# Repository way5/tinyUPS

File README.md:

<h1>

`tinyUPS` a tiny toolkit for your UPS

</h1>

<p align="center" style="text-align:center">

&nbsp;&nbsp;&nbsp;&nbsp;&nbsp;&nbsp;

</p>

## **+ DESCRIPTION**

**tinyUPS** is the way to extend functionality of an Uninterruptible Power Supply (UPS)/power inverters.
It provides onboard SNMP server, temperature control and a Control Panel (CP), just like on an enterprise systems.
The project is now on beta test stage, however it shows very stable results during months 24/7. If you'll decide to modify your own UPS it's at your own risk.

<table cellpadding="0" cellspacing="0" width="100%">
<tr style="border-bottom: 1px solid;">
<td width="50px" style="text-align:center; padding-top:20px;">

</td>
<td>

This project requires advanced skills in electronics. It's not a plug-n-play device. ;)

</td>
</tr>
<tr>
<td style="text-align:center; padding-top:20px;">

</td>
<td>

**Follow the standard precautions! Uninterruptible Power Supply (UPS) is a potentially dangerous device as it contains electric parts under high voltage.**

</td>
</tr>
</table>

## **+ TABLE OF CONTENTS**

+ [**+ DESCRIPTION**](#-description)
+ [**+ TABLE OF CONTENTS**](#-table-of-contents)
+ [**+ TOOLKIT**](#-toolkit)
  + [- CONTROLLER](#--controller)
  + [- PCB](#--pcb)
  + [- Web UI](#--web-ui)
+ [**+ BUILD**](#-build)
  + [- CONFIGURATION](#--configuration)
  + [- WiFi CONNECTION STRATEGIES](#--wifi-connection-strategies)
+ [**+ SETUP**](#-setup)
+ [**+ CONTROL PANEL**](#-control-panel)
+ [**+ DEVELOPMENT**](#-development)
  + [- DRIVERS](#--drivers)
  + [- DEBUG](#--debug)
+ [**+ PHOTOS**](#-photos)
+ [**+ CREDITS**](#-credits)

## **+ TOOLKIT**

- PlatformIO
- KiCAD

### - CONTROLLER
**tinyUPS** is originally based on [WEMOS S2 mini](https://www.wemos.cc/en/latest/s2/s2_mini.html) board. However, very likely it would work on another ESP32 boards with minor changes in firmware.
All the configuration you may need is in [platformio.ini](platformio.ini) and the UPS driver header file. If the communication interface of a particular UPS is not SPI, you need to create a new UPS driver and to change the PCB as well.

<table cellpadding="0" cellspacing="0" width="100%">
<tr>
<td width="50px" style="text-align:center; padding-top:20px;">

</td>
<td>

If you've created a new driver please share it by creating merge request or attaching it in discussions.

</td>
</tr>
</table>

### - PCB
The [current PCB](schematics/CAM/tinyUPS.kicad_pcb) is designed for DIY via CAM method. If you want it printed profesionally, you may need to redesign the PCB.
Since the most of the UPS controllers have 5V data bus, we need a level shifter to be able to communicate with them and a small step-down PSU for ESP32.

[Bill of materials](schematics/CAM/tinyUPS.csv). Instead of the BSS138 mosfets could be used any compatible type, ex.: IRLML2502.

If you'll be using `S2 mini` board you need to desolder built-in LDO IC (ME6211C33) since power will be supplied directly to 3.3V pin. It's possible to keep the LDO but you will not be able to use serial port for firmware upload and debugging. See [WEMOS S2 mini schematics](schematics/sch_s2_mini_v1.0.0.pdf).

The example driver is for a built in SPI LCD display, for a particular manufacturer and model.
You'll probably have the very different device and may be even without any LCD display, so you'd need to figure out how to speak with the controller. This part is DIY. Feel free to call for help in [Discussions](https://github.com/way5/tinyUPS/discussions).

### - Web UI

UI translations are available in [./web/lang](./web/lang) directory. You can add new translation or remove existing if you wish by editing the header of [i18n.js](web/src/includes/i18n.js) script. Variable `i18nlang` contains the list of available locales to be built-in, where element 0 of the array is also a fallback (used by default) locale. Remove unnecessary locales from `i18nlang` to save space on file system partition.

The package manager is `yarn` so if you're not familiar with it continue with the folowing to build the UI:

```bash
yarn build:prod
```

that's all you need to prepare the FS partition to upload. Use `Upload Filesystem Image` command from `PlatformIO` project tasks or:

```bash
platformio run --target uploadfs [--environment [your_env]]
```

## **+ BUILD**

### - CONFIGURATION

All sigificant parameters for your setup are inside [configrure.json](./configure.json) file. If you're adding a new parameter you'd need to run `Rebuild Intellisense Index` in PlatformIO in order to have your parameter set and available.

| PARAMETER | DESCRIPTION |
|:---|:---|
| system_log_size | Size of the system log file (in bytes) |
| snmp_log_size | Size of the SNMP server log file (in bytes) |
| mtemp_log_size | Size of the temperature management log (in bytes) |
| mdata_log_size | Size of the log of monitored events (in bytes) |
| ups_rated_input_voltage | Nominal input voltage value (V) |
| ups_rated_input_freq | Nominal input frequency (Hz) |
| ups_rated_low_input_voltage_threshold | Nominal low threshold of the input voltage (V) |
| ups_rated_high_input_voltage_threshold | Nominal hight threshold for input voltage (V) |
| ups_rated_output_voltage | Nominal output voltage (V) |
| ups_rated_output_freq | Nominal output frequency (Hz) |
| battery_rated_charge_capacity_ah | Nominal UPS battery capacity (Ah) |
| ups_rated_battery_amps_max | Nominal UPS battery current (Amps) |
| wifi_reconnect_method | WiFi reconnection method (`see below`) |
| wifi_discovered_length | Max. length of the data array of discovered APs |

### - WiFi CONNECTION STRATEGIES

If **tinyUPS** has lost connection with AP you may wish it to fallback to AP mode (`tinyUPS.01.XXXX` network name) or it may keep trying to reconnect till the source network is available.
You can choose the desired behavior (see `wifi_reconnect_method` parameter) before to compile firmware.

| METHOD_ID | DESCRIPTION |
|:---:|:---|
| 1 | If the configuration data is available, **tinyUPS** intents to connect to the specified AP. If the connection is not succeeded it starts AP. If connection is lost the device tryes to reconnect once (10 sec interval). If connection is not succeeded it starts AP and remains in this mode until restart. |
|  2 <sub>[D]</sub> | If **tinyUPS** has lost connection with source network it tryes to reconnect once. If connection is not succeeded it starts AP and periodically scans WiFi networks. If the source network has found, the device intents to reconnect. Unless the connection is succeeded it remains in AP mode. |
| 3 | Once the device has lost connection to AP it continuously tryes to reconnect to the source network. The WiFi mode remains STA. |
| 4 | Rely on built-in functionality of `setAutoReconnect()`. **tinyUPS** will remain in STA mode and be seeking for the source AP. |

>***[D]*** - the default method

## **+ SETUP**
When you first run **tinyUPS**, it boots up in AP mode. Look for `tinyUPS.01.XXXX` WiFi network. Default network password (config.apkey) could be changed in [helpers.h](src/helpers.h). Once connected the configuration is available on 192.168.4.1.

When setup is completed **tinyUPS** restarts, expecting an automatically assigned IP.

You are able to restart the device or reset configuration data to defaults using Control Panel -> Service Menu:

and then continue with confirmation:

## **+ CONTROL PANEL**

The UI is pretty simple and displays most of the real-time parameters. There are multiple self explanatory graphical representations for the collected data.

 After successful setup it is highly recommended to change the `AP key` and generate the `device serial number`. Both options and corresponding controls you can find in `Settings` -> `Security` tab and `SNMP` tab respectively.

## **+ DEVELOPMENT**

### - DRIVERS
There are the following functions that must be implemented by every UPS driver: `upsDriverInit, upsDriverLoop, upsDriverDeinit`.
You may also wish to look at the driver for thermistor (currently this is 1k M52A), it may need some changes. Depends on which thermistor you'll be using.

### - DEBUG
Serial monitor is used to perform the most of the tasks and to solve issues. Once you've connected use `?` to list available commands.

## **+ PHOTOS**

|  |  |  |  |  |
|:---:|:---:|:---:|:---:|:---:|

## **+ CREDITS**

- Arduino [SNMP agent](https://github.com/0neblock/Arduino_SNMP) by #0neblock
- [ESPAsyncWebServer](https://github.com/me-no-dev/ESPAsyncWebServer)
- Icons by [Tabler Icons](https://tabler.io/)

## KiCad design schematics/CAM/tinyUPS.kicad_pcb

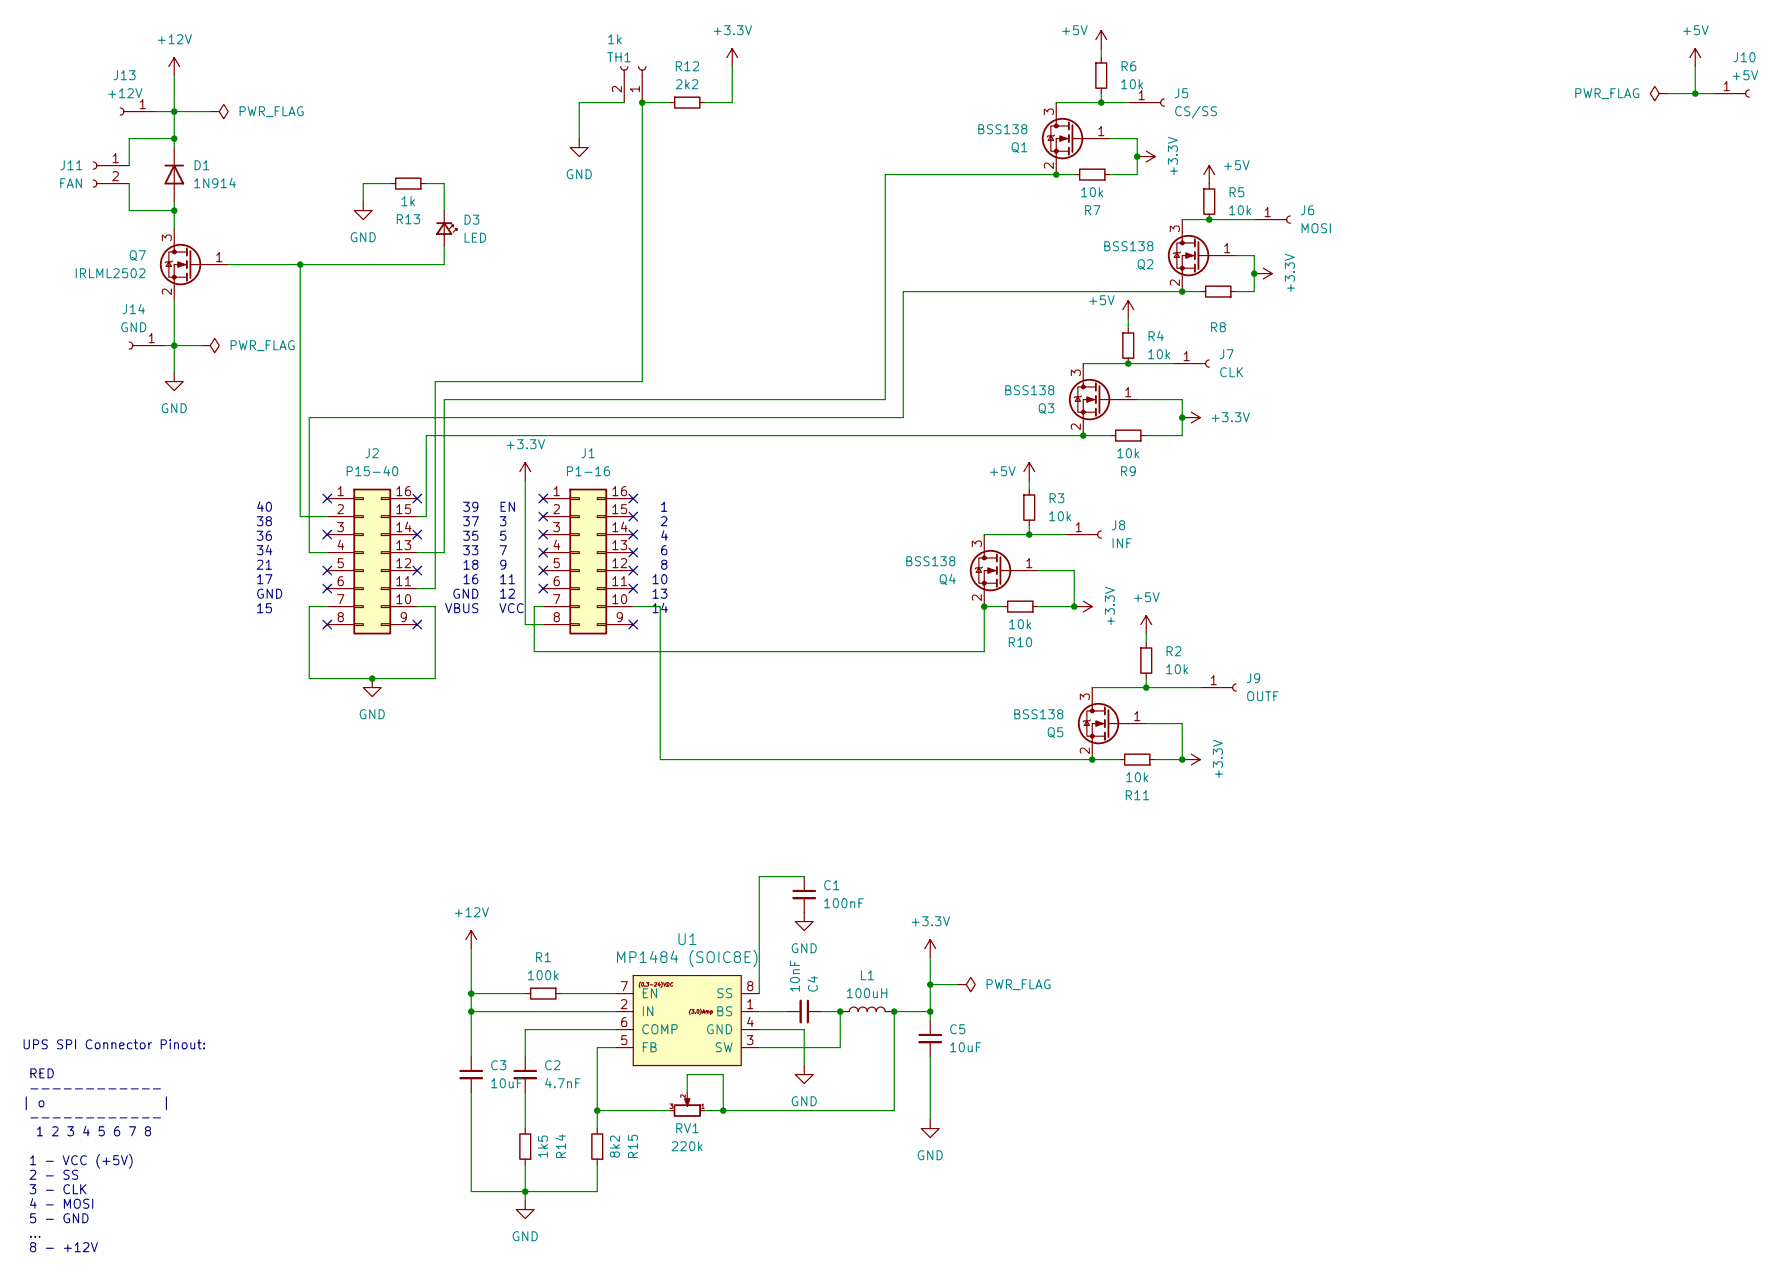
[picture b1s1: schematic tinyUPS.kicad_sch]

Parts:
C1: 100nF; C_1206_3216Metric_Pad1.33x1.80mm_HandSolder
C2: 4.7nF; C_1206_3216Metric_Pad1.33x1.80mm_HandSolder
C3, C5: 10uF; C_1206_3216Metric_Pad1.33x1.80mm_HandSolder
C4: 10nF; C_1206_3216Metric_Pad1.33x1.80mm_HandSolder
D1: 1N914; D_1210_3225Metric_Pad1.42x2.65mm_HandSolder
D3: LED; LED_1206_3216Metric_Pad1.42x1.75mm_HandSolder
J1: P1-16; PinHeader_2x08_P2.54mm_Vertical
J2: P15-40; PinHeader_2x08_P2.54mm_Vertical
J5: CS/SS; PinHeader_1x01_P2.54mm_Vertical
J6: MOSI; PinHeader_1x01_P2.54mm_Vertical
J7: CLK; PinHeader_1x01_P2.54mm_Vertical
J8: INF; PinHeader_1x01_P2.54mm_Vertical
J9: OUTF; PinHeader_1x01_P2.54mm_Vertical
J10: +5V; PinHeader_1x01_P2.54mm_Vertical
J11: FAN; PinHeader_1x02_P2.54mm_Vertical
J13: +12V; PinHeader_1x01_P2.54mm_Vertical
J14: GND; PinHeader_1x01_P2.54mm_Vertical
L1: 100uH; L_Bourns-SRN8040_8x8.15mm
Q1, Q2, Q3, Q4, Q5: BSS138; SOT-23_Handsoldering
Q7: IRLML2502; SOT-23W_Handsoldering
R1: 100k; R_1206_3216Metric_Pad1.30x1.75mm_HandSolder
R2, R3, R4, R5, R6, R7, R8, R9, R10, R11: 10k; R_1206_3216Metric_Pad1.30x1.75mm_HandSolder
R12: 2k2; R_Axial_DIN0207_L6.3mm_D2.5mm_P7.62mm_Horizontal
R13: 1k; R_1206_3216Metric_Pad1.30x1.75mm_HandSolder
R14: 1k5; R_1206_3216Metric_Pad1.30x1.75mm_HandSolder
R15: 8k2; R_1206_3216Metric_Pad1.30x1.75mm_HandSolder
RV1: 220k; Potentiometer_Bourns_3224W_Vertical
TH1: 1k; PinHeader_1x02_P2.54mm_Vertical
U1: MP1484 (SOIC8E); SOIC-8_3.9x4.9mm_P1.27mm

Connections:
+3.3V: C5.1, J1.8, L1.2, Q1.1 (G), Q2.1 (G), Q3.1 (G), Q4.1 (G), Q5.1 (G), R7.1, R8.1, R9.1, R10.1, R11.1, R12.2, RV1.1, RV1.2
+5V: J10.1, R2.1, R3.1, R4.1, R5.1, R6.1
+12V: C3.1, D1.1 (K), J11.1, J13.1, R1.2, U1.2 (IN)
GND: C1.2, C3.2, C5.2, J2.7, J2.10, J14.1, Q7.2 (S), R13.2, R14.1, R15.1, TH1.2, U1.4 (GND)
unnamed: C2.2, R14.2
unnamed: D1.2 (A), J11.2, Q7.3 (D)
unnamed: D3.2 (A), J2.2, Q7.1 (G)
unnamed: D3.1 (K), R13.1
unnamed: J1.7, Q4.2 (S), R10.2
unnamed: J1.10, Q5.2 (S), R11.2
unnamed: J2.4, Q2.2 (S), R8.2
unnamed: J2.11, R12.1, TH1.1
unnamed: J2.13, Q1.2 (S), R7.2
unnamed: J2.15, Q3.2 (S), R9.2
unnamed: J5.1, Q1.3 (D), R6.2
unnamed: J6.1, Q2.3 (D), R5.2
unnamed: J7.1, Q3.3 (D), R4.2
unnamed: J8.1, Q4.3 (D), R3.2
unnamed: J9.1, Q5.3 (D), R2.2
unnamed: C4.2, U1.1 (BS)
unnamed: C2.1, U1.6 (COMP)
unnamed: R1.1, U1.7 (EN)
unnamed: R15.2, RV1.3, U1.5 (FB)
unnamed: C1.1, U1.8 (SS)
unnamed: C4.1, L1.1, U1.3 (SW)

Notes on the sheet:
40 38 36 34 21 17 GND 15
39 37 35 33 18 16 GND VBUS
1 2 4 6 8 10 13 14
EN 3 5 7 9 11 12 VCC
UPS SPI Connector Pinout: RED ------------ | o | ------------ 1 2 3 4 5 6 7 8 1 - VCC (+5V) 2 - SS 3 - CLK 4 - MOSI 5 - GND ... 8 - +12V

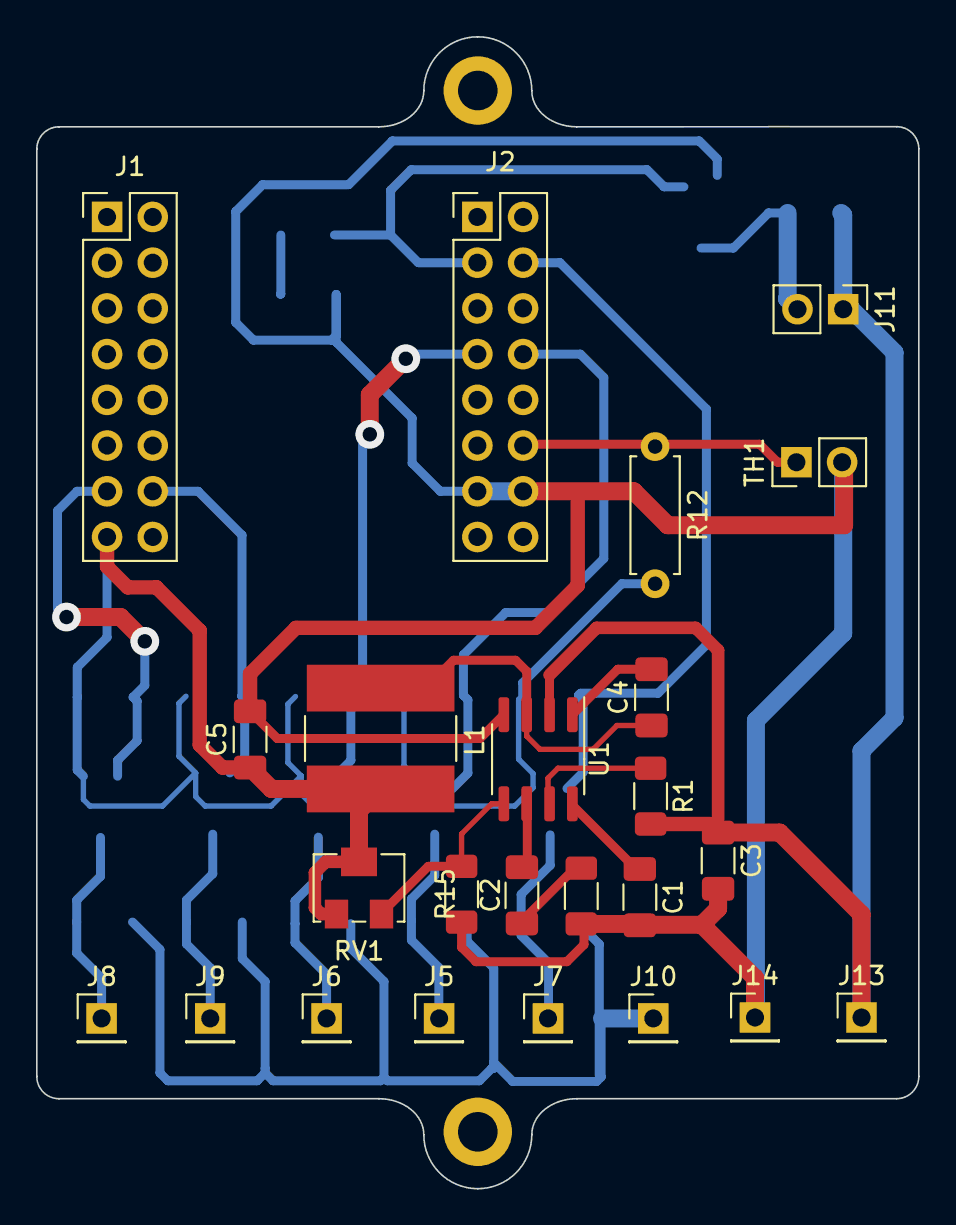
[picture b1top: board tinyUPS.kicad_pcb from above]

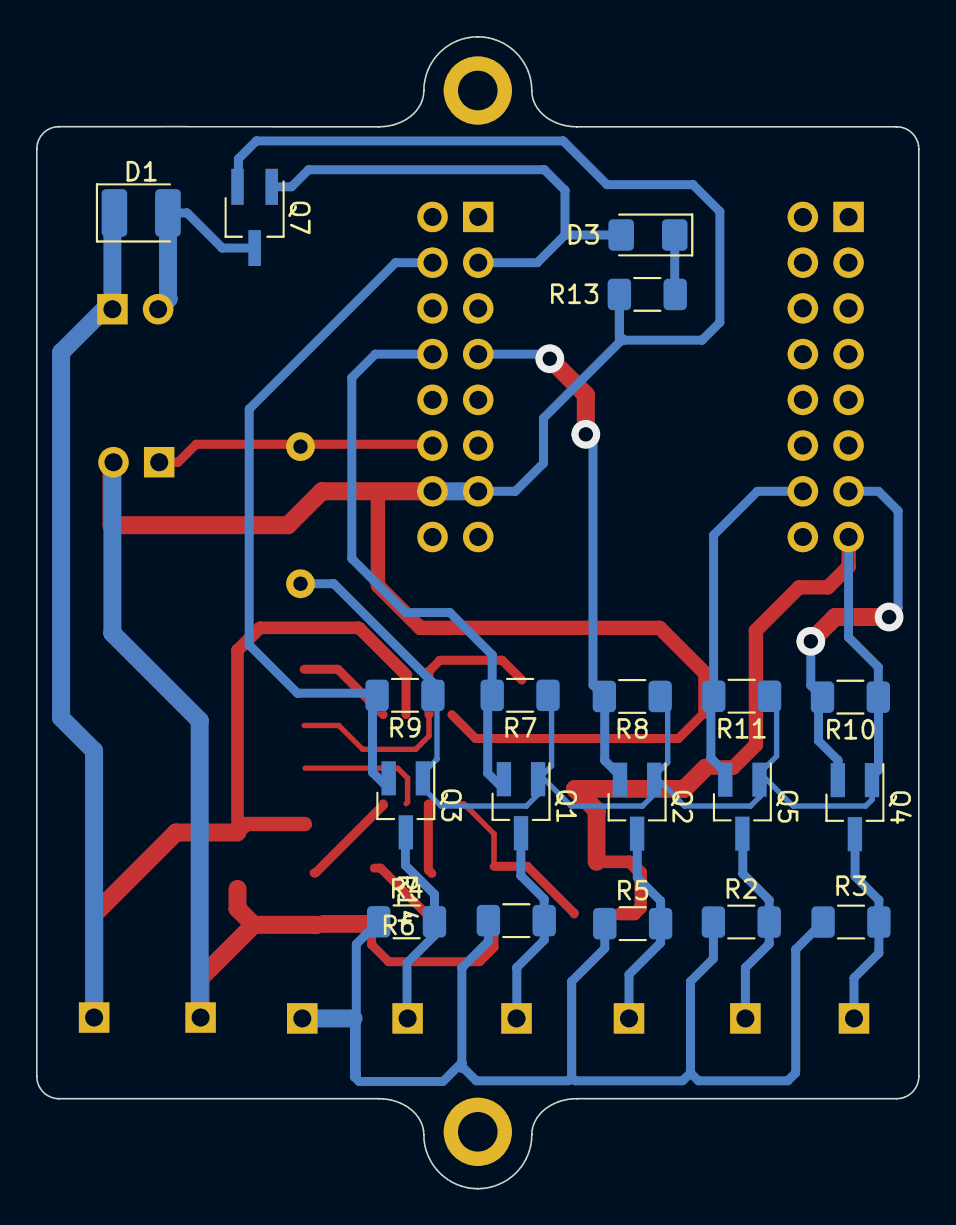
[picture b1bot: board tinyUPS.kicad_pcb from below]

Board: 2 copper layers, 49.0 x 64.0 mm, 43 parts (19 on the bottom side), 25 nets.

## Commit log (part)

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2023-07-06 v1.0.0
2023-08-01 UI update, bug fixes, v1.1.0
2023-08-03 fixes and improvements
2023-08-05 ui upgrade
2023-08-11 plurality, pm. optimization
2023-09-05 overal optimization, bugfixes, legacy code cleanup
2023-09-06 readme update
2023-09-27 overall enhancements
2024-01-09 OTA, improvements and fixes
2025-03-19 firmware: stability improvements and bug fixes. disabled json api. web: rolling bask without json API. web interface improvements and fixes. New functionality added. Charts are now functional. Packag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
2025-03-19 code cleanup
2025-03-19 atomic fix for project urls
2025-03-20 fix firmware ID in SNMP
2025-06-08 SDK update, UI update, memory leak fixes
2025-06-08 battery lifetime fix + improvements
2025-09-03 stability improvements, UI update

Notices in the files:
README.md:
https://img.shields.io/badge/License%3A-GPL--3.0-orange?style=flat&logo=gnu&logoColor=white
